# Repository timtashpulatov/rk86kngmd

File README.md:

# rk86kngmd

A replica of 1993 floppy disc controller for "Radio-86RK" computers. Built around 8255 parallel port adapter and a handful of discrete logic chips.

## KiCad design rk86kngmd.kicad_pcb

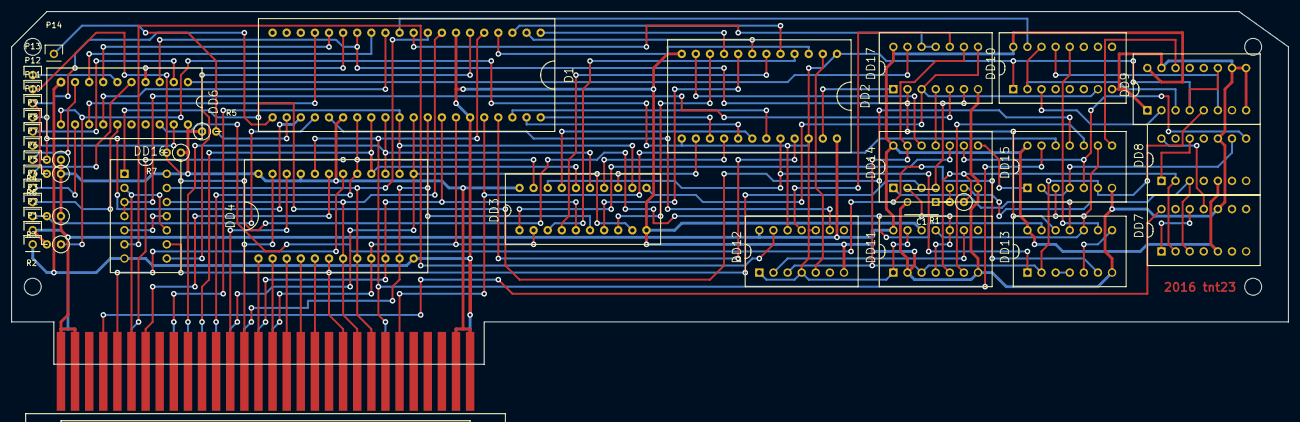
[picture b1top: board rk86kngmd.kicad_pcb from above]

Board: 2 copper layers, 226.2 x 62.5 mm, 39 parts (0 on the bottom side), 101 nets.

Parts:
C1: 100; C_Disc_D6_P5
D1: К580ВВ55; DIP40-2.5mm
DD2: К555ИР13; DIP24-2.5mm
DD3: К555ИР23; DIP20-2.5mm
DD4: 2716; DIP24-2.5mm
DD6: К555ИР22; DIP20-2.5mm
DD7, DD8: К555ИЕ5; DIP14-2.5mm
DD9: К555ИЕ7; DIP16-2.5mm
DD10: К555ИД4; DIP16-2.5mm
DD11, DD12: К555ТМ2; DIP14-2.5mm
DD13: К555ЛА3; DIP14-2.5mm
DD14: К555ЛН1; DIP14-2.5mm
DD15: К555ЛИ1; DIP14-2.5mm
DD16: К555ЛЛ1; DIP14-2.5mm
DD17: К555ЛЕ1; DIP14-2.5mm
P1, P2, P3, P4, P5, P6, P7, P8, P9, P10, P11, P12, P13, P14: CONN_01X01; Pin_Header_Straight_1x01
R1: 200; Resistor_Vertical_RM2_5mm
R2, R3, R4, R5, R6, R7: 1K; Resistor_Vertical_RM2_5mm
X1: ОНп-КС-23

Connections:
+5V: D1.26, DD2.24, DD3.20, DD4.21, DD4.24, DD6.20, DD7.5, DD8.5, DD9.16, DD10.16, DD11.14, DD12.14, DD13.14, DD14.14, DD15.14, DD16.14, DD17.14, P2.1, R2.2, R3.1, R4.1, R5.1, R6.1, R7.1, X1.B1, X1.B2, X1.B29, X1.B30
/17: DD2.11, DD14.12
/18: DD3.1, DD14.10
/A0: D1.9, DD4.8, DD16.13, X1.B8
/A1: D1.8, DD4.7, DD16.12, X1.B9
/A2: DD4.6, DD14.3, DD16.9, X1.B10
/A3: DD4.5, X1.B12
/A4: DD4.4, X1.B13
/A5: DD4.3, X1.B14
/A6: DD4.2, X1.B15
/A7: DD4.1, X1.B16
/A8: DD4.23, X1.B17
/A9: DD4.22, X1.B18
/A10: DD4.19, X1.B24
/CS1: DD4.18, X1.B26
/CS3: DD16.2, DD16.10, X1.B25
/D0: D1.34, DD3.2, DD4.9, X1.A15
/D1: D1.33, DD3.5, DD4.10, X1.A16
/D2: D1.32, DD3.6, DD4.11, X1.A17
/D3: D1.31, DD3.9, DD4.13, X1.A18
/D4: D1.30, DD3.12, DD4.14, X1.A22
/D5: D1.29, DD3.15, DD4.15, X1.A21
/D6: D1.28, DD3.16, DD4.16, X1.A20
/D7: D1.27, DD3.19, DD4.17, X1.A19
/OSC: DD7.14, X1.B27
/PB7: D1.25, DD12.9
/PC1: D1.15, DD6.4
/PC2: D1.16, DD6.7
/PC3: D1.17, DD6.13
/PC4: D1.13, DD6.8
/PC5: D1.12, DD6.14
/PC6: D1.11, DD10.15
/PC7: D1.10, DD17.11, DD17.12
/RD: D1.5, DD4.20, DD15.13, X1.A7
/WR: D1.36, DD15.12, X1.B6
/WRDATA: DD6.18, DD13.6
/WRGATE: D1.14, DD6.3, DD13.12, DD17.2
DIR: DD6.5, P6.1
DISC_A: DD6.15, P4.1
DISC_B: DD6.12, P5.1
GND: C1.2, D1.7, D1.35, DD2.12, DD3.10, DD4.12, DD6.10, DD7.10, DD8.10, DD9.1, DD9.8, DD9.9, DD9.10, DD9.15, DD10.8, DD11.2, DD11.7, DD11.12, DD12.7, DD13.7, DD14.7, DD15.7, DD16.7, DD17.7, P1.1, X1.A1, X1.A2, X1.A29, X1.A30
IP: D1.24, P3.1, R3.2
unnamed: C1.1, DD14.5, R1.2
unnamed: D1.1, DD2.9
unnamed: D1.2, DD2.7
unnamed: D1.3, DD2.5
unnamed: D1.4, DD2.3
unnamed: D1.6, DD16.8
unnamed: D1.37, DD2.21
unnamed: D1.38, DD2.19
unnamed: D1.39, DD2.17
unnamed: D1.40, DD2.15
unnamed: DD2.4, DD3.3
unnamed: DD2.6, DD3.4
unnamed: DD2.8, DD3.7
unnamed: DD2.10, DD3.8
unnamed: DD2.14, DD3.13
unnamed: DD2.16, DD3.14
unnamed: DD2.18, DD3.17
unnamed: DD7.1, DD7.12
unnamed: DD7.11, DD8.14
unnamed: DD8.1, DD8.12
unnamed: DD2.1, DD2.13, DD2.22, DD6.11, DD9.4, DD9.11, DD10.1, DD11.1, DD11.13, DD12.1, DD12.4, DD12.10, DD12.12, R2.1
unnamed: DD9.2, DD10.3
unnamed: DD3.11, DD10.7, DD17.3, DD17.8
unnamed: DD10.12, DD13.9
unnamed: DD9.6, DD10.13
unnamed: DD9.3, DD10.2, DD10.14
unnamed: DD9.5, DD11.3, DD12.3, DD13.2, DD14.13, DD15.6, DD17.9
unnamed: DD7.2, DD8.2, DD11.5, R1.1
unnamed: DD11.6, DD15.10
unnamed: DD11.9, DD12.2
unnamed: DD11.4, DD11.10, DD14.2
unnamed: DD11.11, DD13.10, DD15.3, DD15.9
unnamed: DD2.2, DD12.5
unnamed: DD12.11, DD17.10
unnamed: DD12.13, DD16.6
unnamed: DD2.20, DD3.18, DD13.1
unnamed: DD13.3, DD13.4
unnamed: DD13.5, DD13.8
unnamed: DD13.11, DD14.1
unnamed: DD14.4, DD17.6
unnamed: DD7.3, DD8.3, DD14.6
unnamed: DD14.8, DD15.1
unnamed: DD8.8, DD14.9, DD15.5
unnamed: DD14.11, DD17.4
unnamed: DD8.9, DD15.2, DD15.4
unnamed: DD9.14, DD15.8
unnamed: DD15.11, DD16.1
unnamed: DD16.3, DD16.4, DD17.5
unnamed: DD16.5, DD16.11
unnamed: DD2.23, DD17.1
unnamed: DD6.1, DD17.13
RD_DATA: DD13.13, P12.1, R7.2
READY: D1.22, P14.1, R5.2
SIDE: DD6.6, P13.1
STEP: DD6.9, P7.1
TR00: D1.23, P10.1, R4.2
WPRT: D1.21, P11.1, R6.2
WR_DATA: DD6.19, P8.1
WR_GATE: DD6.2, P9.1

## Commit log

2016-05-07 DIP40 footprint fixed
2016-05-07 Project file update
2016-05-07 Schematic changes
2016-05-07 Fixed lib name in schematics
2016-05-15 Timing diagram added
2016-05-15 (lib) Logic symbols minor update
2016-05-22 Schematic minor updates
2016-05-22 sources folder
2016-05-22 Added RK header
2016-05-22 Minor update
2016-05-22 binaries
2017-01-14 Gerbers exported
2017-05-30 Added credentials
2017-05-30 Gerbers update
2017-05-30 PCB minor update
2017-07-04 Added 3d model for vertical TH resistor
2017-07-04 Updated PCB for vertical TH resistors
2017-07-04 Updated 3d models for DIP-14
2017-07-04 Updated 3d models for other DIP chips
2017-07-24 Add 26-pin floppy FPC connector footprint
2017-07-24 Assy text updated
2017-07-24 3D pic added
